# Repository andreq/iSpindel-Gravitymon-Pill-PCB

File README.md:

# iSpindel Gravitymon Pill PCB
 A PCB used to build an iSpindel or GravityMon hydrometer that fit into a popular brand Pill casing instead of a PETling container.  
 Compatible with D1 Mini, C3, S2 and S3 mini esp board.

# Building tips
 Use the same components as most iSpindel PCB found online.  
 Remove the pin header plastic on the D1 mini (or equivalent) pins.  
 The D1 Mini need to be soldered as close as possible to the Pill PCB (between 1.5 to 1.9mm spacing between both board; Less is better).  
 The battery holder metal tabs need to be cut slightly to fit on the Pill PCB smaller pads.  
 Follow iSpindle build instructor for most of the other parts.  
 Only install the 470k voltade divider resitor for Esp32 based boards (C3, S2 and S3 mini).  
 The switch lever should be far away from the Pill casing, but might need to be shortened depanding on your switch.

# THIS IS A WIP !!!
 The latest PCB itteration was not produced yet, but should fit in a Pill casing.  
 My initial prototype needed a bit of sanding, will update as soon as first rev is tested.  
 I've only tested with a D1 mini, but the schematic and pcb fit Gravitiymon requirements for C3, S2 and S3 Mini.

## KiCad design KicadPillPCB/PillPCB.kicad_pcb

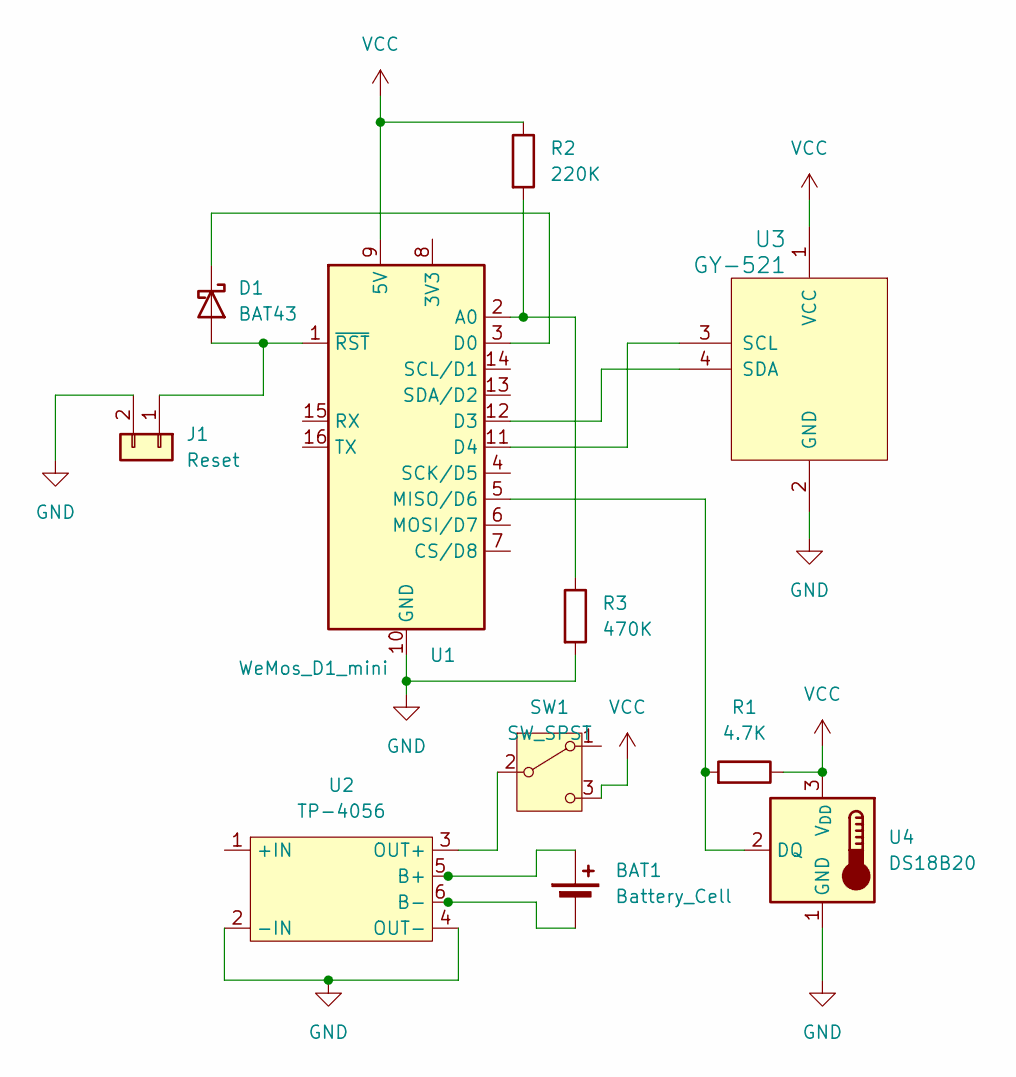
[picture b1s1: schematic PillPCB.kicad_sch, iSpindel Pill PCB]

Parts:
BAT1: Battery_Cell; BatteryHolder_Keystone_1042_1x18650_larger_slot
D1: BAT43; D_DO-35_SOD27_P7.62mm_Horizontal
J1: Reset; PinHeader_1x02_P2.54mm_Vertical
R1: 4.7K; Resistor
R2: 220K; Resistor
R3: 470K; Resistor
SW1: SW_SPST; SW_CuK_OS102011MA1QN1_SPDT_Angled
U1: WeMos_D1_mini; WEMOS_D1_mini_light_less_pins
U2: TP-4056; TP4056-Module
U3: GY-521
U4: DS18B20; TO-92_Inline

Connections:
GND: J1.2, R3.2, U1.10 (GND), U2.2 (-IN), U2.4 (OUT-), U3.2 (GND), U4.1 (GND)
unnamed: BAT1.1 (+), U2.5 (B+)
unnamed: BAT1.2 (-), U2.6 (B-)
unnamed: D1.2 (A), J1.1, U1.1 (~RST)
unnamed: D1.1 (K), U1.3 (D0)
unnamed: SW1.2 (B), U2.3 (OUT+)
unnamed: R2.2, R3.1, U1.2 (A0)
unnamed: U1.12 (D3), U3.4 (SDA)
unnamed: U1.11 (D4), U3.3 (SCL)
unnamed: R1.2, U1.5 (MISO/D6), U4.2 (DQ)
VCC: R1.1, R2.1, SW1.3 (C), U1.9 (5V), U3.1 (VCC), U4.3 (V_{DD})

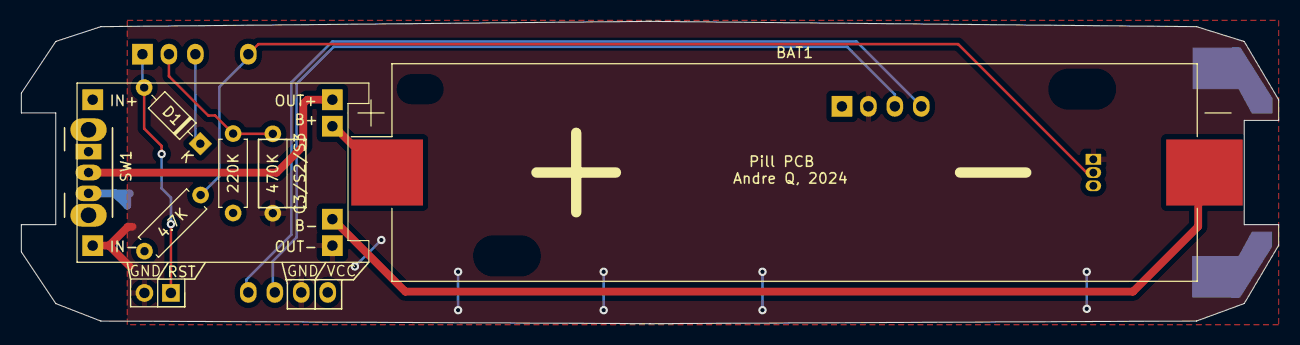
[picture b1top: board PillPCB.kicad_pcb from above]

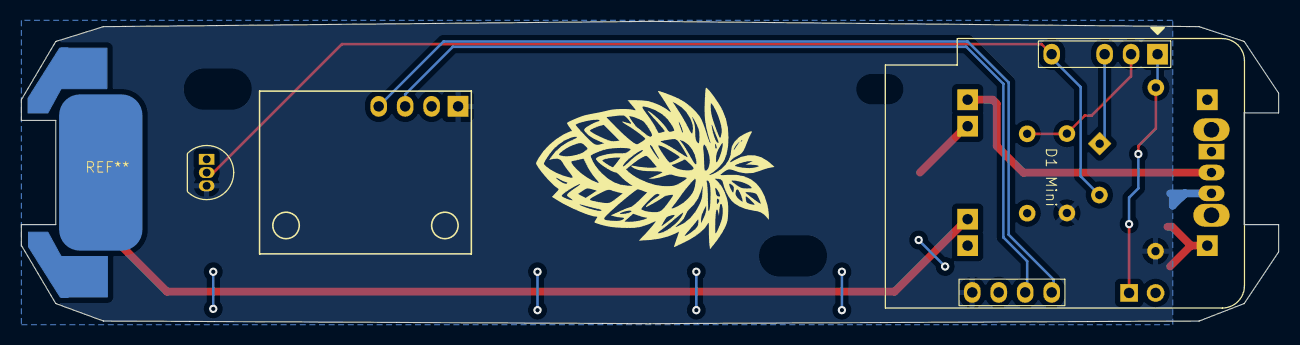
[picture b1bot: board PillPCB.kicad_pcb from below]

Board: 2 copper layers, 120.6 x 29.0 mm, 11 parts (3 on the bottom side), 11 nets.

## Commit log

2024-06-06 Finalizing the first PCB Rev
    - Tweaked PCB cutout to fit better in pill casing
    - Added RST pads for easier soldering
    - Added hop logo and info on silkscreen
    - Moved USB charger to give room for thin usb qi receiver plug
2024-06-06 Update README.md
    - Added Building tips
    - Added warning about this being a WIP
